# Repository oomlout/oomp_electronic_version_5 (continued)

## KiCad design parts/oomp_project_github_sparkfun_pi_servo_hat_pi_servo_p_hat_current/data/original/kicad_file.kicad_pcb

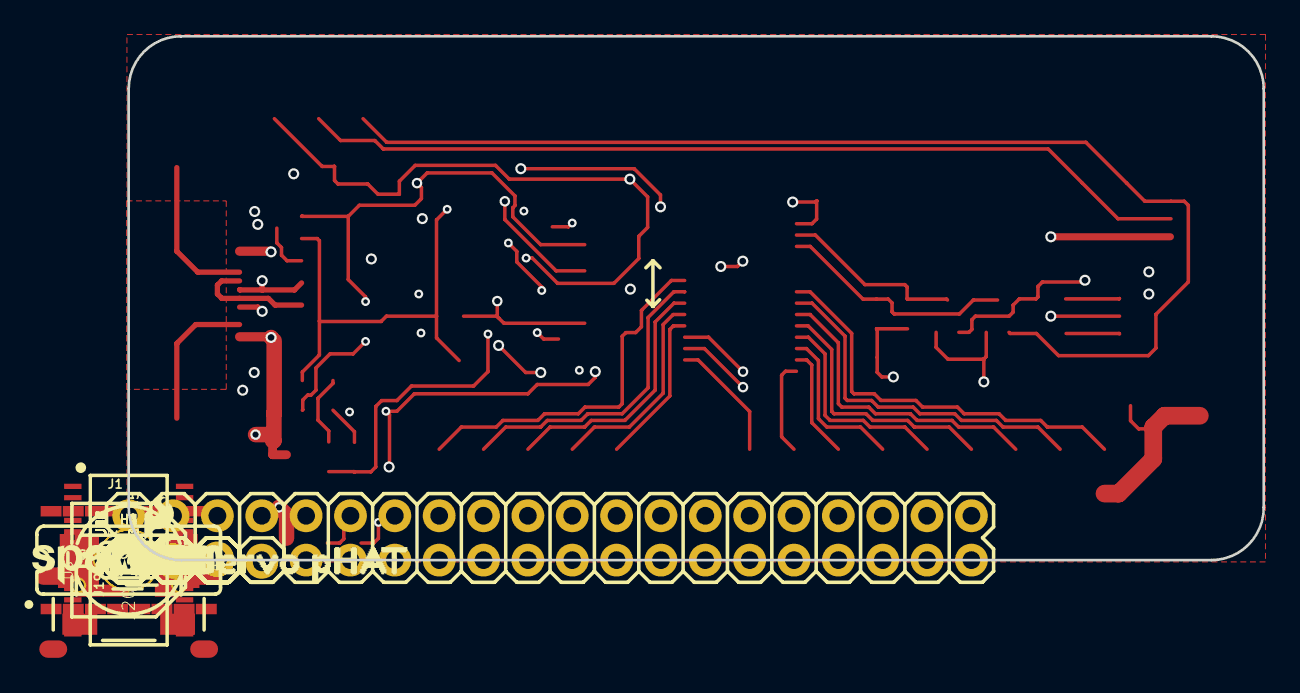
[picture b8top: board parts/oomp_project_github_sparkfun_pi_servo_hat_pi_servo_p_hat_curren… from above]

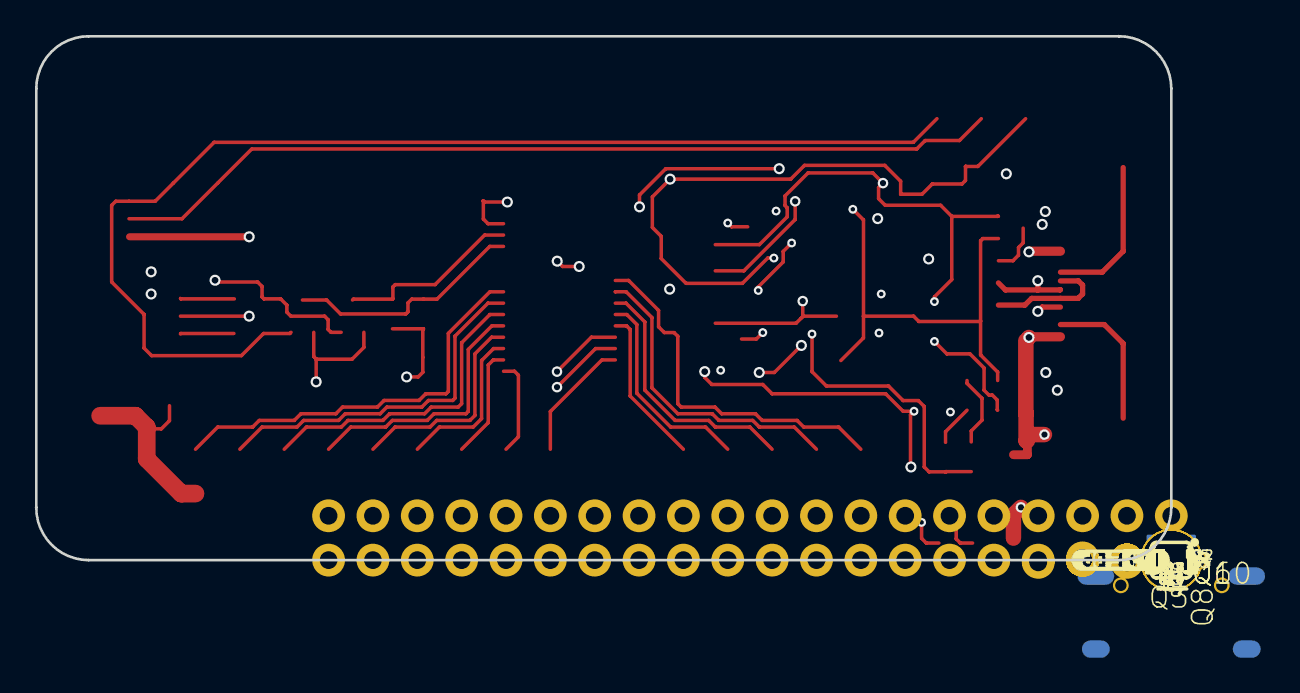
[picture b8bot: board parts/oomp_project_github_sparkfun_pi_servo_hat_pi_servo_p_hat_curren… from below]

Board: 4 copper layers, 65.0 x 30.0 mm, 148 parts (52 on the bottom side), 54 nets.

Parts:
C3, C4, C6, C7, C8, C10: 0.1uF; 0603
C5: 100uF; PANASONIC_D
C17: 10nF; 0603
D1: GREEN; LED-0603
D2: Yellow; LED-0603
F2: 16V/2.5A(5A TRIP); 1812
FD1, FD2, FD3, FD4: FIDUCIALUFIDUCIAL; FIDUCIAL-MICRO
FRAME2: FRAME-LEDGER; CREATIVE_COMMONS
H1, H2, H3, H4: STAND-OFF
J1: RASPBERRYPI-40-PIN-GPIO; 2X20
J3, J4, J5, J6, J7, J8, J9, J10, J11, J12, J13, J14, J15, J16, J17, J18: 1X03
J19: QWIIC; JST04_1MM_RA
J20: USB C; USB-C-16P
J21: RVR; 1X04_LOCK
JP2: FUSE BP; SMT-JUMPER_2_NO_SILK
JP3: I2C; SMT-JUMPER_3_2-NC_TRACE_SILK
JP4: PI ISO; SMT-JUMPER_2_NC_TRACE_SILK
LOGO1: SFE_LOGO_NAME_FLAME.1_INCH; SFE_LOGO_NAME_FLAME_.1
LOGO2: OSHW-LOGOS; OSHW-LOGO-S
Q1, Q4: 310mA/60V/1.6Ω; SOT323
Q2, Q5, Q7, Q9, Q12: 20V/4.2A/52mΩ/1.4W; SOT23-3
Q3, Q6, Q8, Q10: SOT363_PHILIPS
Q11: SC70-6
R1, R2, R4, R5, R6, R8, R13, R15, R19, R20, R21: 10k; 0603
R3, R7, R9, R14: 47k; 0603
R10, R11: 5.1k; 0603
R12: 330; 0603
R16: 1k; 0603
R17, R18: 240; 0603
S1: SWITCH_SPST_SMD_A
TP0, TP1, TP2, TP3, TP4, TP5, TP6, TP7, TP8, TP9, TP10, TP11, TP12, TP13, TP14, TP15, TP16, TP17, TP20, TP21, TP22, TP23, TP24, TP25, TP26: PAD.03X.04
TP18, TP19: TP_15TH
U1: PCA9685; TSSOP-28_4MM
U2: SN74LVC1G32DCKR; SOT353
U3: CH340C; SO016
U$1: QWIIC_LOGO_5MM; QWIIC_5MM
U$2: I_SUPER2_C-()-03
U$3: 028
U$4: 129
U$5: 230
U$6: 331
U$7: 432
U$8: 533
U$9: 634
U$10: 735
U$11: 836
U$12: 937
U$13: 1038
U$14: 1139
U$15: 1240
U$16: 1341
U$17: 1442
U$18: 1543
U$20, U$24: 5V5
U$21: SIG2
U$22: SIG3
U$23: GND25
U$25: TXO0
U$26: PI#RXI2
U$27: #5V3
U$28: GND2
U$30: RASP_μPI_HAT_SPECIFICATION
U$31: RVR1
U$32: ISO1
U$33: _RXI_0
U$34: USB0
U$35: PI0
U$36: RX0
U$37: TX1
U$38: RVR0
U$39: FUSE_BP0
U$40: G_0
U$41: PI_SERVO_PHAT0

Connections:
3.3V: C3.1, C7.1, J1.1, J1.17, J19.2, JP3.2, Q1.1, Q4.1, R12.2, R16.2, TP22.P$1, U3.16
CC1: J20.A5, R11.2
CC2: J20.B5, R10.2
CH0: J3.3, TP0.P$1, U1.6
CH1: J4.3, TP1.P$1, U1.7
CH2: J5.3, TP2.P$1, U1.8
CH3: J6.3, TP3.P$1, U1.9
CH4: J7.3, TP4.P$1, U1.10
CH5: J8.3, TP5.P$1, U1.11
CH6: J9.3, TP6.P$1, U1.12
CH7: J10.3, TP7.P$1, U1.13
CH8: J11.3, TP8.P$1, U1.15
CH9: J12.3, TP9.P$1, U1.16
CH10: J13.3, TP10.P$1, U1.17
CH11: J14.3, TP11.P$1, U1.18
CH12: J15.3, TP12.P$1, U1.19
CH13: J16.3, TP13.P$1, U1.20
CH14: J17.3, TP14.P$1, U1.21
CH15: J18.3, TP15.P$1, U1.22
CH340-TXO: D1.C, S1.1, TP23.P$1, U3.2
D+: J20.A6, J20.B6, U3.5
D-: J20.A7, J20.B7, U3.6
GND: C3.2, C4.2, C5.-, C6.2, C7.2, C8.2, C10.2, C17.2, J1.6, J1.9, J1.14, J1.20, J1.25, J1.30, J1.34, J1.39, J3.1, J4.1, J5.1, J6.1, J7.1, J8.1, J9.1, J10.1, J11.1, J12.1, J13.1, J14.1, J15.1, J16.1, J17.1, J18.1, J19.1, J20.GND, J20.GND2, J21.3, Q11.1, Q11.4, R3.1, R6.1, R7.1, R8.1, R9.1, R10.1, R11.1, R13.1, R14.1, R15.1, R20.1, R21.1, TP17.P$1, U1.14, U1.23, U1.25, U2.3, U3.1
LV_SCL: J1.5, J19.4, Q1.2, R4.1, TP18.P$1
LV_SDA: J1.3, J19.3, Q4.2, R5.1, TP19.P$1
unnamed: Q5.1, Q6.3, R7.2
unnamed: JP3.3, R4.2
unnamed: Q1.3, R2.1, U1.26
unnamed: Q4.3, R1.1, U1.27
unnamed: JP3.1, R5.2
unnamed: D2.A, R16.1
unnamed: D1.A, R12.1
unnamed: Q11.2, R17.2
unnamed: Q2.1, Q3.3, R3.2
unnamed: Q3.2, Q3.5, Q3.6, R6.2
unnamed: Q6.2, Q6.5, Q6.6, R8.2
unnamed: Q11.5, Q11.6, R18.1
unnamed: Q11.3, Q12.1, R19.1
unnamed: C17.1, U3.4
unnamed: Q7.1, Q8.3, R9.2
unnamed: Q8.2, Q8.5, Q8.6, R13.2
unnamed: R17.1, U2.4
unnamed: Q9.1, Q10.3, R14.2
unnamed: Q10.2, Q10.5, Q10.6, R15.2
unnamed: J1.2, JP4.2
PI-5V: C4.1, C8.1, JP4.1, Q7.2, Q8.4, Q9.2, Q10.4, Q12.3, R1.2, R2.2, R18.2, R19.2, TP24.P$1, U1.28, U2.5
PI-RXI: J1.10, S1.2, TP26.P$1
PI-TXO: D2.C, J1.8, J21.1, TP20.P$1, U3.3
RVR-5V: J21.4, Q2.3, Q3.1, Q7.3, Q8.1, R20.2, TP25.P$1, U2.1
RVR-TXO: J21.2, S1.3, TP21.P$1
SERVO: C5.+, C6.1, J3.2, J4.2, J5.2, J6.2, J7.2, J8.2, J9.2, J10.2, J11.2, J12.2, J13.2, J14.2, J15.2, J16.2, J17.2, J18.2, Q2.2, Q3.4, Q5.2, Q6.4, Q12.2, TP16.P$1
SHLD: J20.SHLD1, J20.SHLD2, J20.SHLD3, J20.SHLD4, J20.SHLD5, J20.SHLD6, J20.SHLD7, J20.SHLD8
USB-5V: F2.2, JP2.2, Q5.3, Q6.1, Q9.3, Q10.1, R21.2, U2.2
VBUS: C10.1, F2.1, J20.VBUS1, J20.VBUS2, JP2.1
